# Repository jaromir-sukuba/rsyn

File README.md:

# What is in this repository?
Here is the complete set of design files, BOM, source files, test results and other resources that I used in the process of building a simple resistance synthesizer.

# What is resistance synthesizer?
A resistance synthesizer is a device allowing the emulation of a resistance or (nearly) any value for use in control and test instrumentation. It can emulate resistive components like resistive temperature devices (thermistors, platinum sensors) or other resistive sensors, too. There are commercial instruments that do this task, but they are often way outside the average hobby budget. Therefore, I decided to build one.

This project demonstrates a simple resistance synthesizer device built around a high-precision digital-to-analog converter (DAC) that is controlled by a microcontroller, allowing communication with a computer to control and calibrate the instrument, allowing integration into automated test setups. As standard in test equipment, the analog portion of the instrument is isolated from the digital portion, which makes the integration much easier as the synthesizer doesn't suffer from ground loops and is insulated from potentially dangerous voltage levels. Apart from control via USB, the instrument contains a local user interface consisting of a keypad and display.

# How does resistance synthesis work?
Reistance synthesis can be done in numerous ways. The obvious one is a network of resistors and relays to switch the desired value. The number of relays and resistors can be minimized by varying exponential values and switching in binary code patterns. That would employ resistor values of 1R-2R-4R-8R-16,  etc., and an appropriate switching pattern allowing the resistor to be included or excluded from the circuit. This approach is quite straightforward but has a few issues. Contact resistance is included in the resistor value and can matter, especially on the low end of the range (unless a four-wire arrangement is used, which can solve most of the contact problems); the contact resistance may change over the relay lifetime and other environmental factors. Furthermore, switching takes time, may be acoustically noisy, and causes relay contact wear.
More elegant is the electrical resistance adjustment. Digital potentiometers may be adequate for many uses, but they usually suffer from low resolution and low precision. While those can be a perfect fit for many applications, my idea of a resistance synthesizer requires somehow a more nuanced approach.
Fortunately, there are other ways to emulate the resistance, reducing the problem to current sensing and voltage generation, both of which can be done relatively easily and with much higher precision than the digital potentiometer can offer.
The principle is simple and this picture demonstrates this approach. 

The left side of the picture captures voltage and current in a simple circuit with a resistor, following Ohm's law. Should we include voltage source U in series with the resistor, the apparent resistance of the circuit changes, following the formula on the right side of the picture. If the Us is derived from the current Ir, the resulting resistance value is invariant of the current Ir, so that the circuit behaves like a resistor with apparent resistance Rs between zero (Us = Ir x Rr) and Rr (Us = 0). 

Second picture depicts this idealized schematic in a way that somehow resembles the circuit in my resistance synthesizer. 

The voltage on Rr is brought to a voltage follower (so that Ir isn't influenced by following circuits) and subsequently to a potentiometer, allowing it to regulate the synthesized resistance value. This circuit has the advantage of a potentiometer acting like a grounded voltage divider, so it can be substituted by a multiplying DAC, in this case LTC2756.

# Instrument overview
Schematic sheet 'Interconnect' depicts top-level schematics and internal instrument wiring.

## Resistance synthesizer board
Reference resistors R19 and R29/30 are switched using DG442 analog switches U11C and U11D. There are options to change the gain of the reference resistor amplifier (R20, R24, R28, and U7B, U11A, and U11B) and DAC amplifier (R8, R9, R10, and switches U7A, U7C, and U7D), but those aren't used in the current firmware, so that U7A and U7B are switched continuously.
U4 is the heart of the resistance synthesizer board. It works in a more-or-less datasheet configuration, with one interesting point: its reference voltage is switchable by zero-ohm resistors R2 and R3 (only one is installed). When R2 is populated, the output works in the range 0..5 V and is useful for testing the DAC. In this mode, the circuit doesn't work as a resistance synthesizer. When R3 is installed instead of R2, the reference voltage is derived from the resistance drop on a reference resistor (refer to Picture #2), and the circuit works as a resistance synthesizer.
The remaining parts of the PCB are just support functions for the DAC. Microcontroller U10 acts as a UART-DAC bridge, converting ASCII commands from serial lines to DAC SPI control packets and analog switch actions. U3 acts as a digital isolator, allowing the digital and analog boards to be separated electrically.

## Display board
Three SCT2024 shift registers with constant current drivers are chained into a 48-bit-long string. Six pieces of dual starburst LED displays are multiplexed in a 1:4 multiplex ratio by the microcontroller U7. This microcontroller communicates via serial line and transforms single ASCII commands into text readable on the display.

## Digital and PSU boards
U5 on this board acts as the main controlling element of the device. It talks to internal microcontrollers (on the resistance synthesizer board and display board) as well as external communication channels via USB. Apart from that, it reads the keyboard to allow direct user control. The majority of the complexity of this part lies in firmware, available on GitHub.
PSU is relatively straight-forward. Both analog and digital sections are fed from separate transformer windings, each with a diode rectifier and voltage regulator. In the case of the digital section, I opted for a Murata OKI-78-SR-33 switching regulator to cut down on heat generated in the PSU.

# Physical construction
Resistance synthesizers and display boards were designed as 4-layer PCBs in KiCAD. Digital PSU and keypad boards were simple enough to be made on a perfboard.
All electrical components are mounted into a CP-15-32 enclosure with custom milled front and back panels. Construction is obvious from the photos.

# Instrument operation
It is operated using either a local interface or serial commands. For the local interface, keys 1 and 2 select the digit to be modified, and keys 3 and 4 perform incrementation or decrementation of the digit. The digit to be modified blinks for approximately 4 seconds. Pressing keys 1 and 2 simultaneously changes the range (10 and 100 kOhm ranges).
For the serial interface, the following commands are implemented in current firmware:

### idn
returns instrument identification
PC->Instrument: idn<LF>
Instrument->PC: RSYN Ver 1.00<LF>

### srv
set resistance value
PC->Instrument: srv 1.234LF>
Instrument->PC: srv 1.234LF>

### grv
set resistance value
PC->Instrument: grv<LF>
Instrument->PC: grv 1.234LF>

### srr
set resistance range (0: 0-10 kOhm; 1: 0-100 kOhm)
PC->Instrument: srr 1LF>
Instrument->PC: srr 1LF>

### grr
Get the resistance range (0: 0-10 kOhm; 1: 0-100 kOhm).
PC->Instrument: grr<LF>
Instrument->PC: grr 1LF>

### scc 
Set the calibration coefficient (the first argument is the coefficient number, the second is the coefficient).
PC->Instrument: scc 2, 3.456LF>
Instrument->PC: scc 2, 3.456LF>

### gcc 
Get the calibration coefficient (the argument is the coefficient number).
PC->Instrument: gcc 2LF>
Instrument->PC: gcc 2, 3.456LF>

### gcd
get a calibration dump
PC->Instrument: gcd<LF>
Instrument->PC: gcc [followed by calibration constants on each line] <LF>

### wmc
write calibration coefficient (into EEPROM memory; previous calibration is overwritten)
PC->Instrument: wcc<LF>
Instrument->PC: wcc<LF>

After first powering up, default calibration constants 0 and 12345 are loaded for offset and gain, respectively. The user needs to replace those constants with valid ones obtained by calibration. For calibration, a ohmmeter, usually in a form of multimeter has to be used. The precision of the resistance synthesizer is determined by he meter used for adjustment. On the other hand, thermal and long time drift is given by design and construction of the device.
The calibration procedure is as follows:
1. Turn on the calibration meter and resistance synthesizer, connect the appropriate leads, and let them warm up (typical precision meters do have a few hours of warmup required).
2, set the meter to the 10 kOhm manual range, set the synthesizer to the 10 kOhm range, and set the synthesizer to 50 kOhm. Adjust the offset to range 0 so that the meter correctly displays 50 ohms.
3. Set the synthesizer to 10 kOhm. Adjust gain at range 0 so that the meter correctly displays 10 kOhm.
4. Repeat steps 2 and 3 if needed.
5, do the same as step 2 on 100 kOhm ranges and adjust offset at range 1.
6. Do the same as step 3, with a 100 kOhm value, and adjust gain at range 1.
7. Repeat steps 4 and 5 if needed.
8. Issue the wmc command to overwrite previous calibration values in the EEPROM.

## Verification
For parameter verification, I performed two tests: a linearity check and short-term stability. 

For the linearity test, I set the values of the DAC converter to values from 0 to 262143 in increments of 32768. I measured the resitance values using an HP34401A multimeter and calculated the difference from the linear fit of the values, expressed in the least significant digits of the value. As apparent from the graph, the typical deviation from linearity is around 0.2 LSB, indicating that the used DAC has very good linearity, and apart from that, linearity isn't degraded by the analog functionality (chosen opamps and reference resistors).
Short-term stability: I measured the value of resistance set to 5 kOhm over the course of one hour. The value was stable within the 20 mOhm range. 

# Resources
A video showing the synthesizer in operation is at https://youtu.be/5EVBY4_3-oE

# Resume
This resistance synthesizer is not a very common target of DIY designs, but nonetheless, it's a useful tool for automatic calibration of test and measurement instruments or as a general-purpose tool for testing and adjusting multimeters, controllers, and similar apparatus.

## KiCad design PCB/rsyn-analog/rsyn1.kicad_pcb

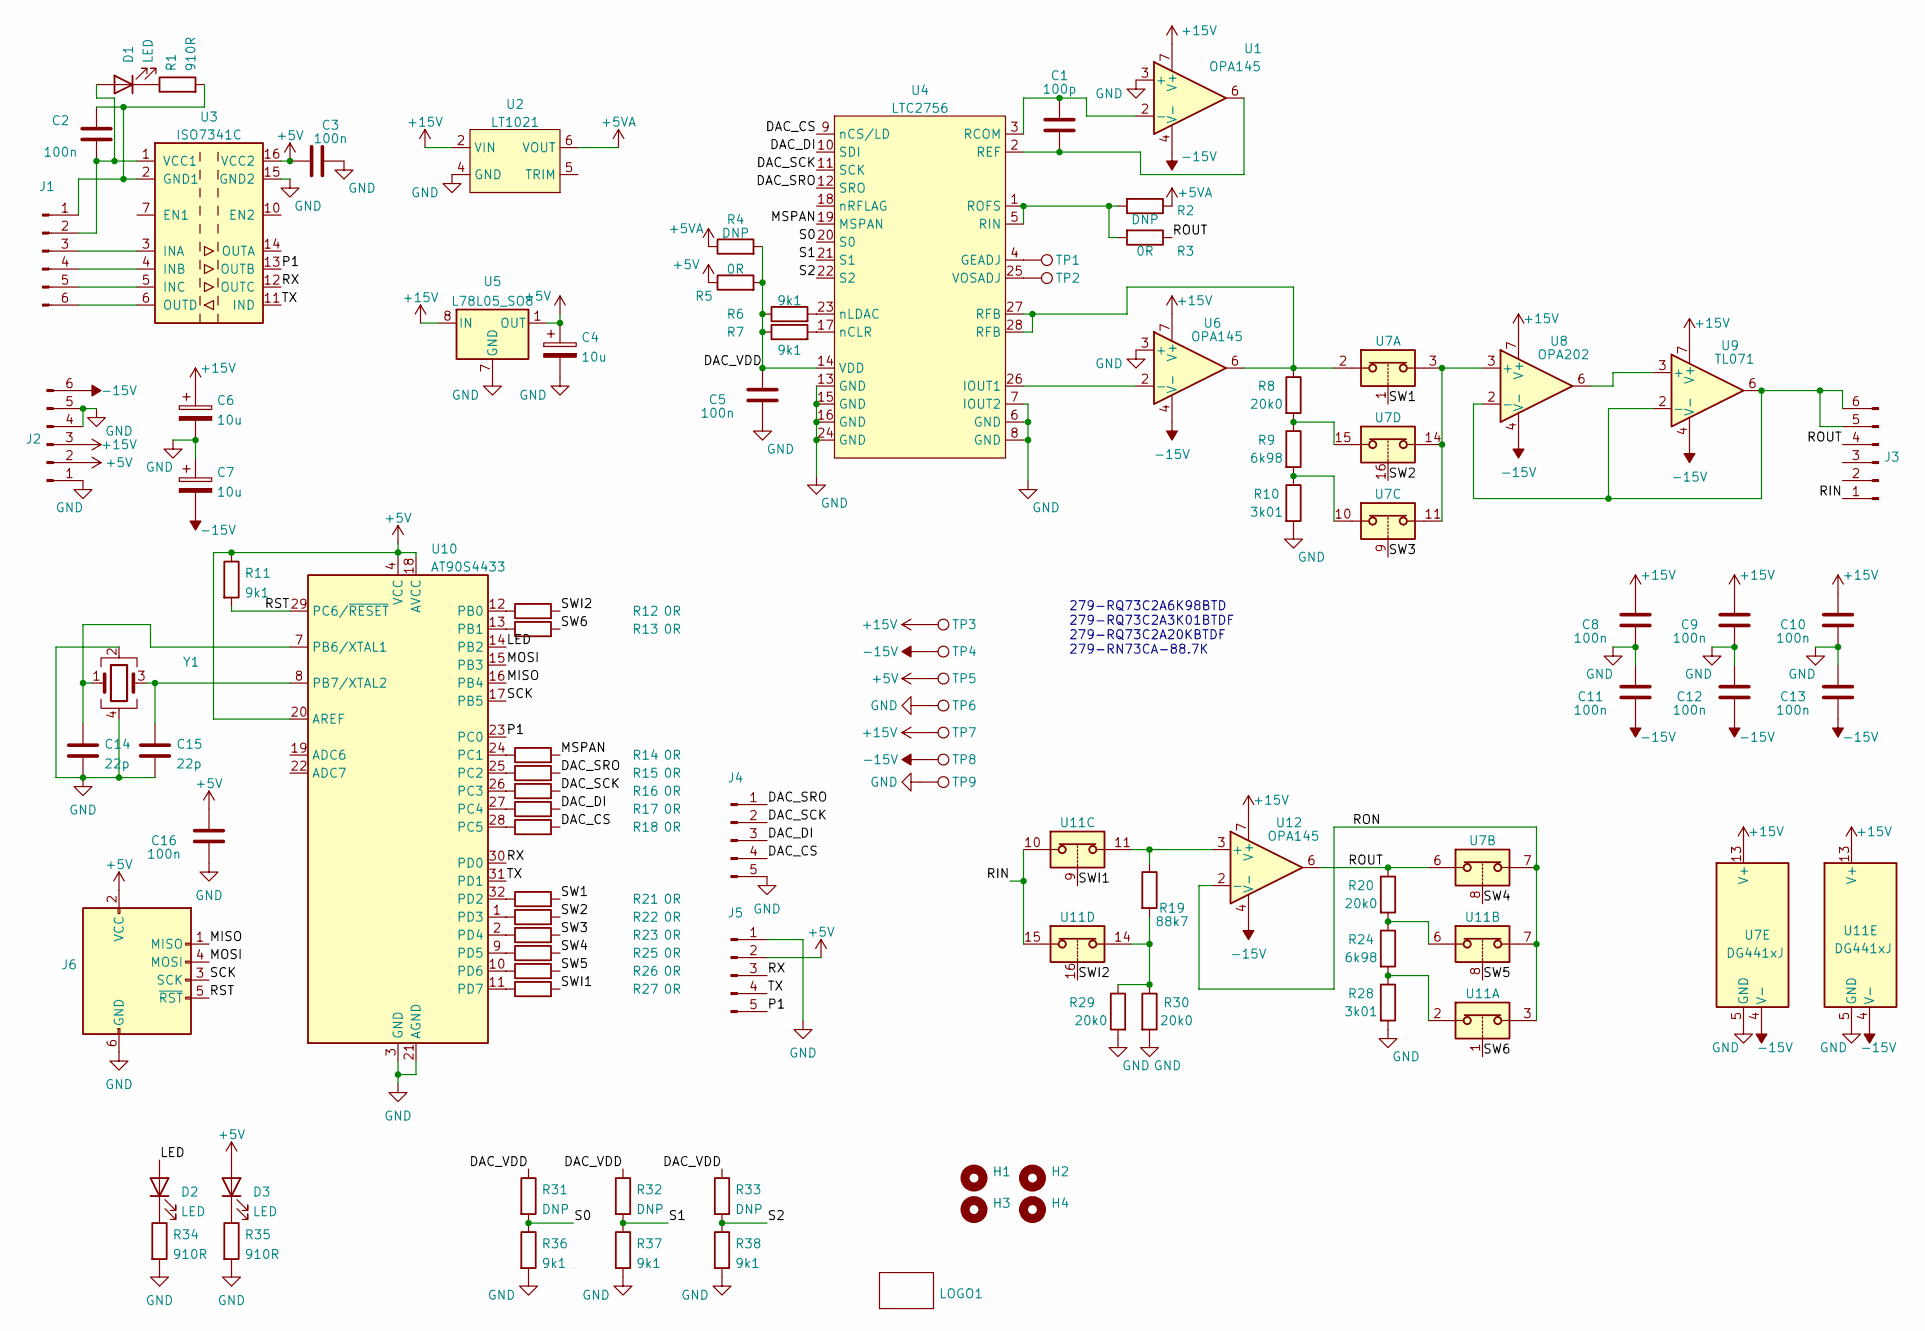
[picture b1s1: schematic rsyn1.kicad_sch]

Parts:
C1: 100p; C_0805_2012Metric_Pad1.18x1.45mm_HandSolder
C2, C3, C5, C8, C9, C10, C11, C12, C13, C16: 100n; C_0805_2012Metric_Pad1.18x1.45mm_HandSolder
C4, C6, C7: 10u; CP_EIA-6032-28_Kemet-C_Pad2.25x2.35mm_HandSolder
C14, C15: 22p; C_0805_2012Metric_Pad1.18x1.45mm_HandSolder
D1, D2, D3: LED; LED_0805_2012Metric_Pad1.15x1.40mm_HandSolder
H1, H2, H3, H4: MountingHole; MountingHole_3.2mm_M3_DIN965_Pad
J1, J2, J3: Conn_01x06_Male; PinHeader_1x06_P2.54mm_Vertical
J4, J5: Conn_01x05_Male; PinHeader_1x05_P2.54mm_Vertical
J6: AVR-ISP-6; IDC-Header_2x03_P2.54mm_Vertical
LOGO1: logo_generic; logo_rpg7x9
R1, R34, R35: 910R; R_0805_2012Metric_Pad1.20x1.40mm_HandSolder
R2, R4, R31, R32, R33: DNP; R_0805_2012Metric_Pad1.20x1.40mm_HandSolder
R3, R5, R12, R13, R14, R15, R16, R17, R18, R21, R22, R23, R25, R26, R27: 0R; R_0805_2012Metric_Pad1.20x1.40mm_HandSolder
R6, R7, R11, R36, R37, R38: 9k1; R_0805_2012Metric_Pad1.20x1.40mm_HandSolder
R8, R20, R29, R30: 20k0; R_0805_2012Metric_Pad1.20x1.40mm_HandSolder
R9, R24: 6k98; R_0805_2012Metric_Pad1.20x1.40mm_HandSolder
R10, R28: 3k01; R_0805_2012Metric_Pad1.20x1.40mm_HandSolder
R19: 88k7; R_0805_2012Metric_Pad1.20x1.40mm_HandSolder
TP1, TP2, TP3, TP4, TP5, TP6, TP7, TP8, TP9: TestPoint; TestPoint_Pad_1.0x1.0mm
U1, U6, U12: OPA145; SOIC-8_3.9x4.9mm_P1.27mm
U2: LT1021; DIP-8_W7.62mm_Socket
U3: ISO7341C; SOIC-16W_7.5x10.3mm_P1.27mm
U4: LTC2756; SSOP-28_5.3x10.2mm_P0.65mm
U5: L78L05_SO8; SOIC-8_3.9x4.9mm_P1.27mm
U7, U11: DG441xJ; SO-16_3.9x9.9mm_P1.27mm
U8: OPA202; SOIC-8_3.9x4.9mm_P1.27mm
U9: TL071; SOIC-8_3.9x4.9mm_P1.27mm
U10: AT90S4433; TQFP-32_7x7mm_P0.8mm
Y1: Crystal_GND24; Crystal_SMD_Abracon_ABM3B-4Pin_5.0x3.2mm

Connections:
+5V: C3.1, C4.1, C16.2, D3.2 (A), J2.2, J5.2, J6.2 (VCC), R5.1, R11.1, TP5.1, U3.16 (VCC2), U5.1 (OUT), U10.4 (VCC), U10.6 (VCC), U10.18 (AVCC), U10.20 (AREF)
+5VA: R2.1, R4.1, U2.6 (VOUT)
+15V: C6.1, C8.2, C9.2, C10.2, J2.3, TP3.1, TP7.1, U1.7 (V+), U2.2 (VIN), U5.8 (IN), U6.7 (V+), U7.13 (V+), U8.7 (V+), U9.7 (V+), U11.13 (V+), U12.7 (V+)
-15V: C7.2, C11.1, C12.1, C13.1, J2.6, TP4.1, TP8.1, U1.4 (V-), U6.4 (V-), U7.4 (V-), U8.4 (V-), U9.4 (V-), U11.4 (V-), U12.4 (V-)
/DAC_CS: J4.4, R18.2, U4.9 (nCS/LD)
/DAC_DI: J4.3, R17.2, U4.10 (SDI)
/DAC_SCK: J4.2, R16.2, U4.11 (SCK)
/DAC_SRO: J4.1, R15.2, U4.12 (SRO)
/DAC_VDD: C5.2, R4.2, R5.2, R6.1, R7.1, R31.1, R32.1, R33.1, U4.14 (VDD)
/LED: D2.2 (A), U10.14 (PB2)
/MISO: J6.1 (MISO), U10.16 (PB4)
/MOSI: J6.4 (MOSI), U10.15 (PB3)
/MSPAN: R14.2, U4.19 (MSPAN)
/P1: J5.5, U3.13 (OUTB), U10.23 (PC0)
/RIN: J3.1, U11.10, U11.15
/RON: U7.7, U11.3, U11.7, U12.2 (-)
/ROUT: J3.4, R3.1, R20.1, U7.6, U12.6
/RST: J6.5 (~RST), R11.2, U10.29 (PC6/~RESET)
/RX: J5.3, U3.12 (OUTC), U10.30 (PD0)
/S0: R31.2, R36.1, U4.20 (S0)
/S1: R32.2, R37.1, U4.21 (S1)
/S2: R33.2, R38.1, U4.22 (S2)
/SCK: J6.3 (SCK), U10.17 (PB5)
/SW1: R21.2, U7.1
/SW2: R22.2, U7.16
/SW3: R23.2, U7.9
/SW4: R25.2, U7.8
/SW5: R26.2, U11.8
/SW6: R13.2, U11.1
/SWI1: R27.2, U11.9
/SWI2: R12.2, U11.16
/TX: J5.4, U3.11 (IND), U10.31 (PD1)
GND: C3.2, C4.2, C5.1, C6.2, C7.1, C8.1, C9.1, C10.1, C11.2, C12.2, C13.2, C14.2, C15.2, C16.1, J2.1, J2.4, J2.5, J4.5, J5.1, J6.6 (GND), R10.2, R28.2, R29.2, R30.2, R34.2, R35.2, R36.2, R37.2, R38.2, TP6.1, TP9.1, U1.3 (+), U2.4 (GND), U3.9 (GND2), U3.15 (GND2), U4.6 (GND), U4.7 (IOUT2), U4.8 (GND), U4.13 (GND), U4.15 (GND), U4.16 (GND), U4.24 (GND), U5.2 (GND), U5.3 (GND), U5.6 (GND), U5.7 (GND), U6.3 (+), U7.5 (GND), U10.3 (GND), U10.5 (GND), U10.21 (AGND), U11.5 (GND), Y1.2, Y1.4
unnamed: C2.1, D1.2 (A), J1.2, U3.1 (VCC1)
unnamed: D1.1 (K), R1.1
unnamed: D2.1 (K), R34.1
unnamed: D3.1 (K), R35.1
unnamed: C2.2, J1.1, R1.2, U3.2 (GND1), U3.8 (GND1)
unnamed: J1.3, U3.3 (INA)
unnamed: J1.4, U3.4 (INB)
unnamed: J1.5, U3.5 (INC)
unnamed: J1.6, U3.6 (OUTD)
unnamed: J3.5, J3.6, U8.2 (-), U9.2 (-), U9.6
unnamed: R8.1, U4.27 (RFB), U4.28 (RFB), U6.6, U7.2
unnamed: R8.2, R9.1, U7.15
unnamed: R9.2, R10.1, U7.10
unnamed: R19.2, R29.1, R30.1, U11.14
unnamed: R20.2, R24.1, U11.6
unnamed: R24.2, R28.1, U11.2
unnamed: C1.2, U1.2 (-), U4.3 (RCOM)
unnamed: TP1.1, U4.4 (GEADJ)
unnamed: U4.26 (IOUT1), U6.2 (-)
unnamed: C1.1, U1.6, U4.2 (REF)
unnamed: R2.2, R3.2, U4.1 (ROFS), U4.5 (RIN)
unnamed: TP2.1, U4.25 (VOSADJ)
unnamed: R7.2, U4.17 (nCLR)
unnamed: R6.2, U4.23 (nLDAC)
unnamed: U7.3, U7.11, U7.14, U8.3 (+)
unnamed: U8.6, U9.3 (+)
unnamed: R12.1, U10.12 (PB0)
unnamed: R13.1, U10.13 (PB1)
unnamed: C14.1, U10.7 (PB6/XTAL1), Y1.1
unnamed: C15.1, U10.8 (PB7/XTAL2), Y1.3
unnamed: R14.1, U10.24 (PC1)
unnamed: R15.1, U10.25 (PC2)
unnamed: R16.1, U10.26 (PC3)
unnamed: R17.1, U10.27 (PC4)
unnamed: R18.1, U10.28 (PC5)
unnamed: R21.1, U10.32 (PD2)
unnamed: R22.1, U10.1 (PD3)
unnamed: R23.1, U10.2 (PD4)
unnamed: R25.1, U10.9 (PD5)
unnamed: R26.1, U10.10 (PD6)
unnamed: R27.1, U10.11 (PD7)
unnamed: R19.1, U11.11, U12.3 (+)

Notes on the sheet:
279-RQ73C2A6K98BTD 279-RQ73C2A3K01BTDF 279-RQ73C2A20KBTDF 279-RN73CA-88.7K

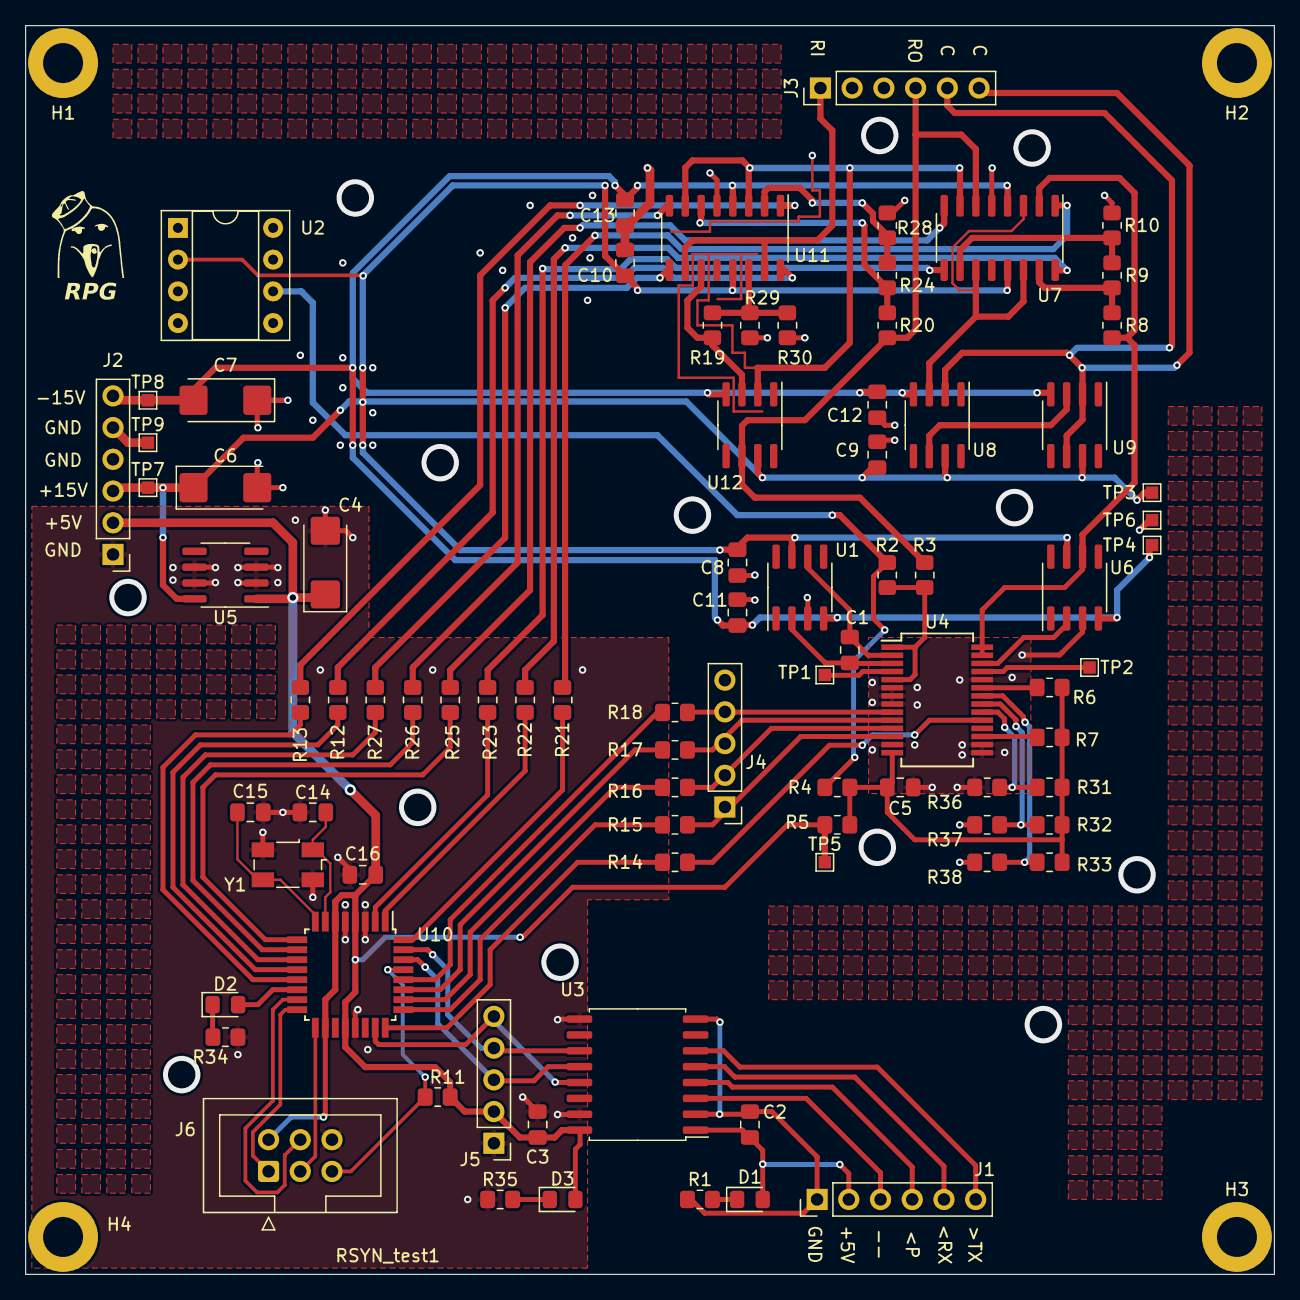
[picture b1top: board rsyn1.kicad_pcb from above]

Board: 4 copper layers, 100.0 x 100.0 mm, 90 parts (0 on the bottom side), 75 nets.

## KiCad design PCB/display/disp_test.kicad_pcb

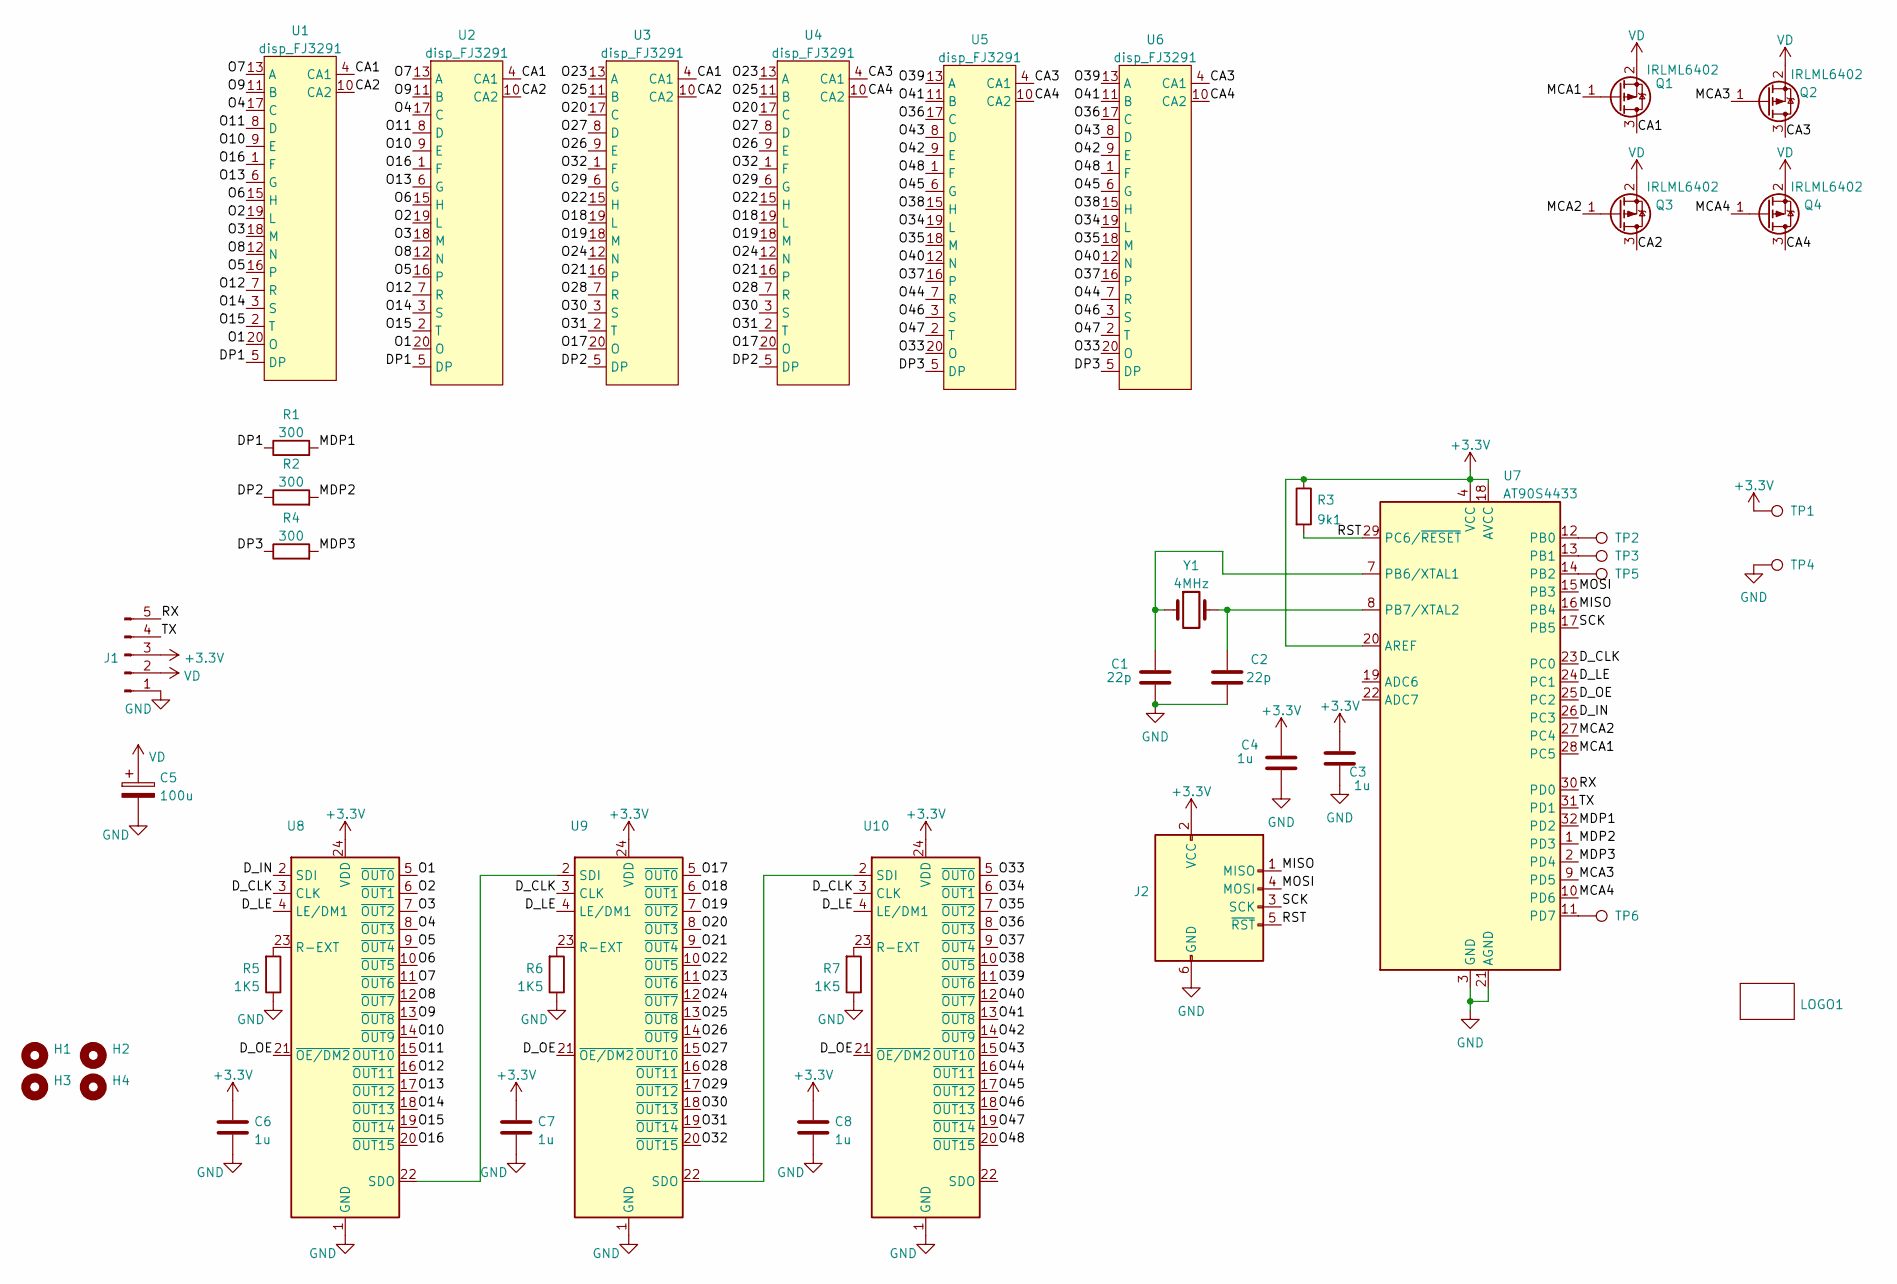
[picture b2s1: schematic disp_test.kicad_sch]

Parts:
C1, C2: 22p; C_0805_2012Metric_Pad1.18x1.45mm_HandSolder
C3, C4, C6, C7, C8: 1u; C_0805_2012Metric_Pad1.18x1.45mm_HandSolder
C5: 100u; CP_EIA-7343-31_Kemet-D_Pad2.25x2.55mm_HandSolder
H1, H2, H3, H4: MountingHole; MountingHole_3.2mm_M3_DIN965_Pad
J1: Conn_01x05_Male; PinHeader_1x05_P2.54mm_Vertical
J2: AVR-ISP-6; IDC-Header_2x03_P2.54mm_Vertical
LOGO1: logo_generic; logo_rpg7x9
Q1, Q2, Q3, Q4: IRLML6402; SOT-23
R1, R2, R4: 300; R_0805_2012Metric_Pad1.20x1.40mm_HandSolder
R3: 9k1; R_0805_2012Metric_Pad1.20x1.40mm_HandSolder
R5, R6, R7: 1K5; R_0805_2012Metric_Pad1.20x1.40mm_HandSolder
TP1, TP2, TP3, TP4, TP5, TP6: TestPoint; TestPoint_Pad_1.0x1.0mm
U1, U2, U3, U4, U5, U6: disp_FJ3291; FJ3291
U7: AT90S4433; TQFP-32_7x7mm_P0.8mm
U8, U9, U10: SSOP-24_3.9x8.7mm_P0.635mm
Y1: 4MHz; Crystal_SMD_HC49-SD_HandSoldering

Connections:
+3.3V: C3.2, C4.2, C6.1, C7.1, C8.1, J1.3, J2.2 (VCC), R3.1, TP1.1, U7.4 (VCC), U7.6 (VCC), U7.18 (AVCC), U7.20 (AREF), U8.24 (VDD), U9.24 (VDD), U10.24 (VDD)
/CA1: Q1.3 (D), U1.4 (CA1), U2.4 (CA1), U3.4 (CA1)
/CA2: Q3.3 (D), U1.10 (CA2), U2.10 (CA2), U3.10 (CA2)
/CA3: Q2.3 (D), U4.4 (CA1), U5.4 (CA1), U6.4 (CA1)
/CA4: Q4.3 (D), U4.10 (CA2), U5.10 (CA2), U6.10 (CA2)
/DP1: R1.1, U1.5 (DP), U2.5 (DP)
/DP2: R2.1, U3.5 (DP), U4.5 (DP)
/DP3: R4.1, U5.5 (DP), U6.5 (DP)
/D_CLK: U7.23 (PC0), U8.3 (CLK), U9.3 (CLK), U10.3 (CLK)
/D_IN: U7.26 (PC3), U8.2 (SDI)
/D_LE: U7.24 (PC1), U8.4 (LE/DM1), U9.4 (LE/DM1), U10.4 (LE/DM1)
/D_OE: U7.25 (PC2), U8.21 (~OE/DM2), U9.21 (~OE/DM2), U10.21 (~OE/DM2)
/MCA1: Q1.1 (G), U7.28 (PC5)
/MCA2: Q3.1 (G), U7.27 (PC4)
/MCA3: Q2.1 (G), U7.9 (PD5)
/MCA4: Q4.1 (G), U7.10 (PD6)
/MDP1: R1.2, U7.32 (PD2)
/MDP2: R2.2, U7.1 (PD3)
/MDP3: R4.2, U7.2 (PD4)
/MISO: J2.1 (MISO), U7.16 (PB4)
/MOSI: J2.4 (MOSI), U7.15 (PB3)
/O1: U1.20 (O), U2.20 (O), U8.5 (~OUT0)
/O2: U1.19 (L), U2.19 (L), U8.6 (~OUT1)
/O3: U1.18 (M), U2.18 (M), U8.7 (~OUT2)
/O4: U1.17 (C), U2.17 (C), U8.8 (~OUT3)
/O5: U1.16, U2.16, U8.9 (~OUT4)
/O6: U1.15 (H), U2.15 (H), U8.10 (~OUT5)
/O7: U1.13 (A), U2.13 (A), U8.11 (~OUT6)
/O8: U1.12 (N), U2.12 (N), U8.12 (~OUT7)
/O9: U1.11 (B), U2.11 (B), U8.13 (~OUT8)
/O10: U1.9 (E), U2.9 (E), U8.14 (~OUT9)
/O11: U1.8 (D), U2.8 (D), U8.15 (~OUT10)
/O12: U1.7 (R), U2.7 (R), U8.16 (~OUT11)
/O13: U1.6 (G), U2.6 (G), U8.17 (~OUT12)
/O14: U1.3 (S), U2.3 (S), U8.18 (~OUT13)
/O15: U1.2 (T), U2.2 (T), U8.19 (~OUT14)
/O16: U1.1 (F), U2.1 (F), U8.20 (~OUT15)
/O17: U3.20 (O), U4.20 (O), U9.5 (~OUT0)
/O18: U3.19 (L), U4.19 (L), U9.6 (~OUT1)
/O19: U3.18 (M), U4.18 (M), U9.7 (~OUT2)
/O20: U3.17 (C), U4.17 (C), U9.8 (~OUT3)
/O21: U3.16, U4.16, U9.9 (~OUT4)
/O22: U3.15 (H), U4.15 (H), U9.10 (~OUT5)
/O23: U3.13 (A), U4.13 (A), U9.11 (~OUT6)
/O24: U3.12 (N), U4.12 (N), U9.12 (~OUT7)
/O25: U3.11 (B), U4.11 (B), U9.13 (~OUT8)
/O26: U3.9 (E), U4.9 (E), U9.14 (~OUT9)
/O27: U3.8 (D), U4.8 (D), U9.15 (~OUT10)
/O28: U3.7 (R), U4.7 (R), U9.16 (~OUT11)
/O29: U3.6 (G), U4.6 (G), U9.17 (~OUT12)
/O30: U3.3 (S), U4.3 (S), U9.18 (~OUT13)
/O31: U3.2 (T), U4.2 (T), U9.19 (~OUT14)
/O32: U3.1 (F), U4.1 (F), U9.20 (~OUT15)
/O33: U5.20 (O), U6.20 (O), U10.5 (~OUT0)
/O34: U5.19 (L), U6.19 (L), U10.6 (~OUT1)
/O35: U5.18 (M), U6.18 (M), U10.7 (~OUT2)
/O36: U5.17 (C), U6.17 (C), U10.8 (~OUT3)
/O37: U5.16, U6.16, U10.9 (~OUT4)
/O38: U5.15 (H), U6.15 (H), U10.10 (~OUT5)
/O39: U5.13 (A), U6.13 (A), U10.11 (~OUT6)
/O40: U5.12 (N), U6.12 (N), U10.12 (~OUT7)
/O41: U5.11 (B), U6.11 (B), U10.13 (~OUT8)
/O42: U5.9 (E), U6.9 (E), U10.14 (~OUT9)
/O43: U5.8 (D), U6.8 (D), U10.15 (~OUT10)
/O44: U5.7 (R), U6.7 (R), U10.16 (~OUT11)
/O45: U5.6 (G), U6.6 (G), U10.17 (~OUT12)
/O46: U5.3 (S), U6.3 (S), U10.18 (~OUT13)
/O47: U5.2 (T), U6.2 (T), U10.19 (~OUT14)
/O48: U5.1 (F), U6.1 (F), U10.20 (~OUT15)
/RST: J2.5 (~RST), R3.2, U7.29 (PC6/~RESET)
/RX: J1.5, U7.30 (PD0)
/SCK: J2.3 (SCK), U7.17 (PB5)
/TX: J1.4, U7.31 (PD1)
GND: C1.2, C2.2, C3.1, C4.1, C5.2, C6.2, C7.2, C8.2, J1.1, J2.6 (GND), R5.1, R6.1, R7.1, TP4.1, U7.3 (GND), U7.5 (GND), U7.21 (AGND), U8.1 (GND), U9.1 (GND), U10.1 (GND)
unnamed: TP2.1, U7.12 (PB0)
unnamed: TP3.1, U7.13 (PB1)
unnamed: TP5.1, U7.14 (PB2)
unnamed: C1.1, U7.7 (PB6/XTAL1), Y1.1
unnamed: C2.1, U7.8 (PB7/XTAL2), Y1.2
unnamed: TP6.1, U7.11 (PD7)
unnamed: R5.2, U8.23 (R-EXT)
unnamed: U8.22 (SDO), U9.2 (SDI)
unnamed: R6.2, U9.23 (R-EXT)
unnamed: R7.2, U10.23 (R-EXT)
unnamed: U9.22 (SDO), U10.2 (SDI)
VD: C5.1, J1.2, Q1.2 (S), Q2.2 (S), Q3.2 (S), Q4.2 (S)

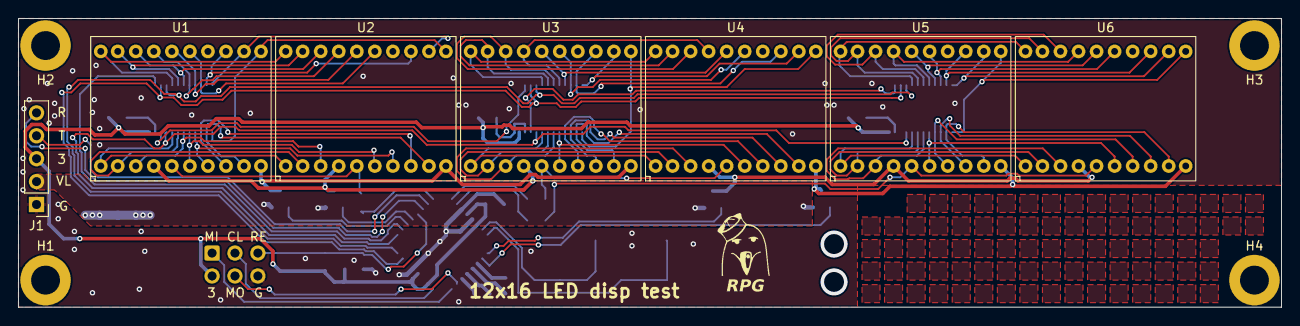
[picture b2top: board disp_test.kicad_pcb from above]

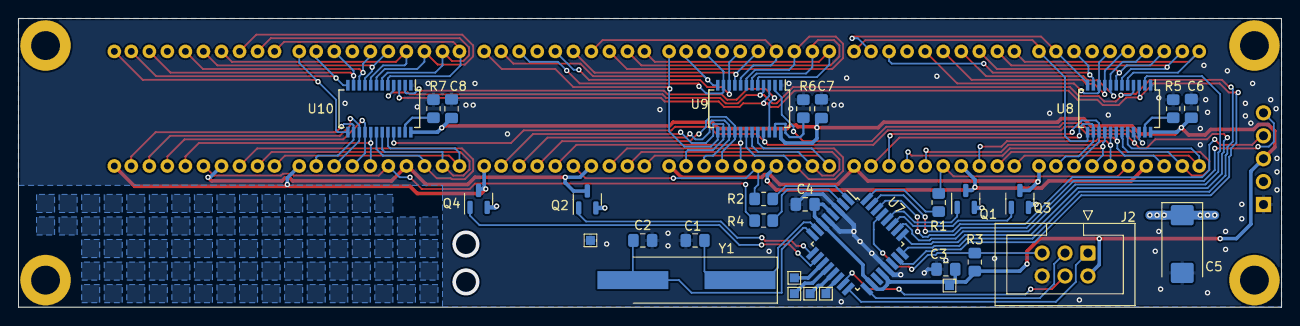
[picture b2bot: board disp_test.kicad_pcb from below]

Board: 2 copper layers, 140.0 x 32.0 mm, 43 parts (31 on the bottom side), 86 nets.

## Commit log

2023-05-17 Build information added.
    Build information added.
2023-05-17 Schematics clarifications
    Updates to schematics, BOM generated
2024-07-11 media added
2024-07-11 added media
